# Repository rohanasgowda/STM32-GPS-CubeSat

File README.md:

# STM32-GPS-CubeSat

Custom STM32-based PCB design featuring GPS-related signal connections and peripheral connectivity, designed using KiCad. This repository contains the KiCad source files, generated manufacturing outputs, bill of materials, design reports, and board visualizations.

## Project overview

The design is centered on an STM32F407VGTx microcontroller. The schematic and board provide labeled connections for GPS- and radio-related signals, microSD, an OLED display, debugging, and power input. The repository documents the PCB design; it does not establish that the board has been assembled, programmed, or functionally tested.

## Project objectives

- Organize the KiCad schematic and PCB design for review and reuse.
- Provide the interfaces and connector signals represented in the schematic, including GPS-, radio-, storage-, display-, debug-, and power-related connections.
- Include the generated Gerber/drill outputs, BOM, design-check reports, and board views alongside the design sources.

These points describe the files in this repository and do not imply verified operation of attached modules or systems.

## Hardware specifications

- **Main component:** STM32F407VGTx, shown as U1 in the schematic and BOM; the BOM identifies an LQFP-100 footprint.
- **Other listed components:** passive capacitors and resistors, a push-button switch, and connectors for the interfaces named below.
- **Power:** the schematic/BOM identify an `EPS_POWER_INPUT` connector. No input-voltage range or power-performance specification is stated in the supplied files.

## PCB design overview

KiCad design sources are in `Hardware/Schematic/` and `Hardware/PCB/`. The supplied fabrication outputs include front- and back-copper, solder-mask, paste, silkscreen, and edge-cut Gerbers. PCB renderings and layer illustrations are provided below.

## Communication interfaces

The schematic labels include:

- **microSD (SPI-labeled signals):** `SD_MOSI`, `SD_MISO`, `SD_SCK`, and `SD_CS`; the BOM lists a `MICROSD_SPI` connector.
- **OLED (I²C-labeled signals):** `OLED_SDA` and `OLED_SCL`; the BOM lists an `OLED_I2C` connector.
- **GPS-related labels:** `GPS_TX`, `GPS_RX`, and `GPS_1PPS`.
- **Radio-related labels:** `RADIO_TX` and `RADIO_RX`.
- **Debug:** `SWDIO'` and `SWCLK` labels and a `SWD_DEBUG` connector are present.

These are labels/connectors in the design files; no protocol configuration, attached module, or functional test result is asserted here.

## PCB 3D visualizations

| Front | Back |
|---|---|
|  |  |

## PCB layout images

| Front layer | Back layer |
|---|---|
|  |  |

## Repository structure

```text
README.md
Hardware/
├── Schematic/       KiCad schematic
├── PCB/             KiCad board and project settings
│   └── Gerber/      Gerbers, drill files, and Gerber job file
├── BOM/             Bill of materials CSV
└── Design_Reports/  ERC and DRC reports
Images/              PCB renderings and layer views
```

## Manufacturing files

Generated manufacturing outputs are in `Hardware/PCB/Gerber/`: the `.gbr` layer files, `.drl` plated/non-plated drill files, and `.gbrjob` job file. Confirm these outputs against the intended manufacturer and the current design before ordering; their presence alone is not a fabrication-readiness claim.

## Design verification

The included ERC report records **0 errors and 0 warnings**. The included DRC report records **0 DRC violations**, but also reports **64 unconnected pads**. These reports are dated 2026-10-23 and are provided as captured; they do not establish that the design is fabrication-ready. Review the unconnected pads and rerun checks on the final design before fabrication.

## Excluded files

KiCad local settings, lock files, autosaves, backups, and temporary files are excluded from version control. The original workspace also contains unrelated documents; they are not part of this repository.

## License

The hardware design files in this repository are provided under the CERN Open Hardware Licence Version 2 - Permissive (CERN-OHL-P-2.0). See [LICENSE](LICENSE) for the full text.

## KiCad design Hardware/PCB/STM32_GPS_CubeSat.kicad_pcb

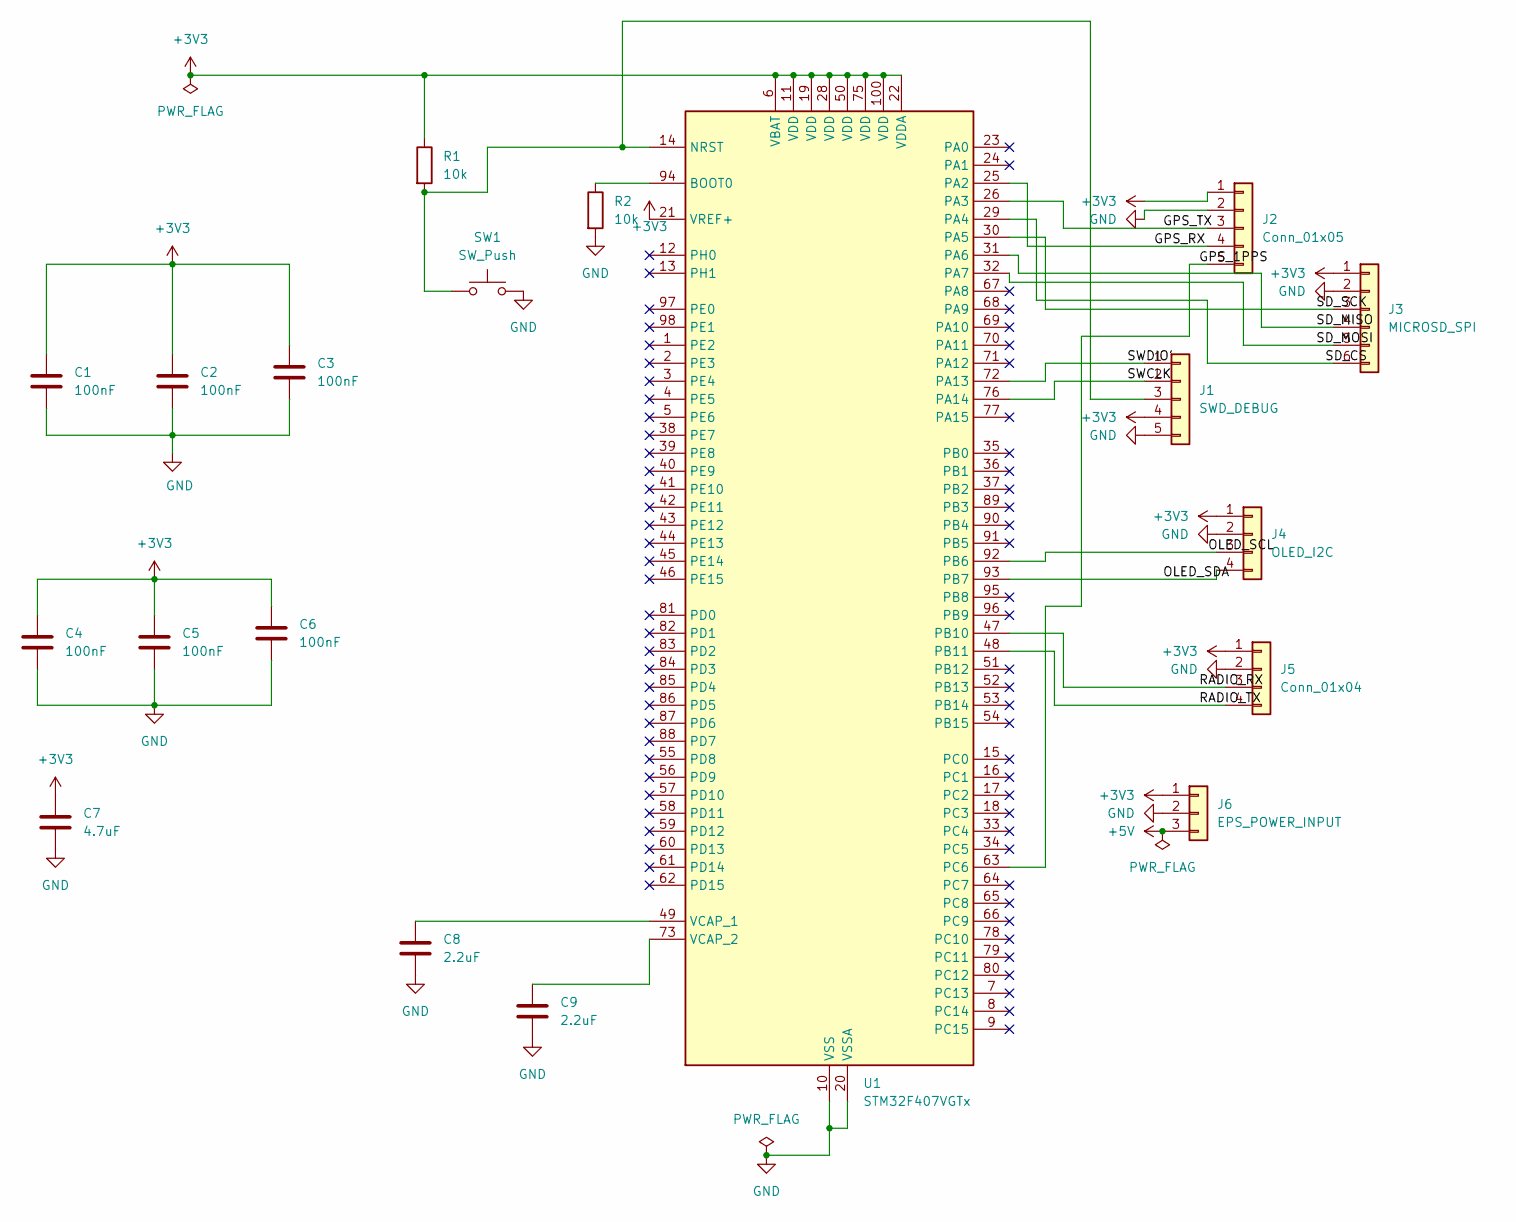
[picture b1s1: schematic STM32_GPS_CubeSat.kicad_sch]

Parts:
C1, C2, C3, C4, C5, C6: 100nF; C_0805_2012Metric
C7: 4.7uF; C_0805_2012Metric
C8, C9: 2.2uF; C_0805_2012Metric
J1: SWD_DEBUG; PinHeader_1x05_P2.54mm_Vertical
J2: Conn_01x05; PinHeader_1x05_P2.54mm_Vertical
J3: MICROSD_SPI; PinHeader_1x06_P2.54mm_Vertical
J4: OLED_I2C; PinHeader_1x04_P2.54mm_Vertical
J5: Conn_01x04; PinHeader_1x04_P2.54mm_Vertical
J6: EPS_POWER_INPUT; PinHeader_1x03_P2.54mm_Vertical
R1, R2: 10k; R_0805_2012Metric
SW1: SW_Push; SW_PUSH_6mm
U1: STM32F407VGTx; LQFP-100_14x14mm_P0.5mm

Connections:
+3V3: C1.1, C2.1, C3.1, C4.1, C5.1, C6.1, C7.1, J1.4, J2.1, J3.1, J4.1, J5.1, J6.1, R1.1, U1.6 (VBAT), U1.11 (VDD), U1.19 (VDD), U1.21 (VREF+), U1.22 (VDDA), U1.28 (VDD), U1.50 (VDD), U1.75 (VDD), U1.100 (VDD)
+5V: J6.3
/GPS_1PPS: J2.5, U1.63 (PC6)
/GPS_RX: J2.4, U1.25 (PA2)
/GPS_TX: J2.3, U1.26 (PA3)
/OLED_SCL: J4.3, U1.92 (PB6)
/OLED_SDA: J4.4, U1.93 (PB7)
/RADIO_RX: J5.3, U1.47 (PB10)
/RADIO_TX: J5.4, U1.48 (PB11)
/SD_CS: J3.6, U1.29 (PA4)
/SD_MISO: J3.4, U1.31 (PA6)
/SD_MOSI: J3.5, U1.32 (PA7)
/SD_SCK: J3.3, U1.30 (PA5)
/SWCLK: J1.2, U1.76 (PA14)
/SWDIO': J1.1, U1.72 (PA13)
GND: C1.2, C2.2, C3.2, C4.2, C5.2, C6.2, C7.2, C8.2, C9.2, J1.5, J2.2, J3.2, J4.2, J5.2, J6.2, R2.2, SW1.2, U1.10 (VSS), U1.20 (VSSA), U1.27 (VSS), U1.74 (VSS), U1.99 (VSS)
unnamed: J1.3, R1.2, SW1.1, U1.14 (NRST)
unnamed: R2.1, U1.94 (BOOT0)
unnamed: C8.1, U1.49 (VCAP_1)
unnamed: C9.1, U1.73 (VCAP_2)

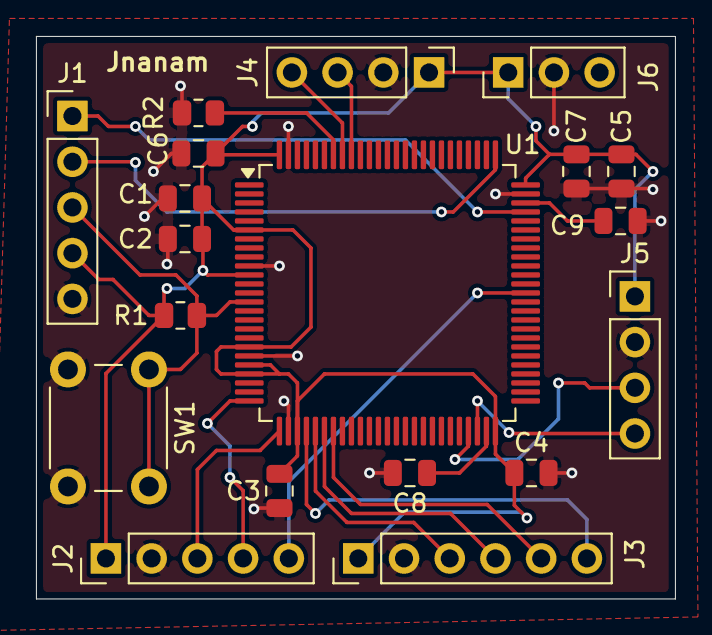
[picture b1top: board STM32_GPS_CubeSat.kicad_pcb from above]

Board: 2 copper layers, 35.5 x 31.2 mm, 19 parts (0 on the bottom side), 19 nets.

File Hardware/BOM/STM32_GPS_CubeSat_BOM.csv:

"Reference","Qty","Value","DNP","Exclude from BOM","Exclude from Board","Exclude from Simulation","Exclude from Position Files","Footprint","Datasheet"
"C1,C2,C3,C4,C5,C6","6","100nF","","","","","${EXCLUDE_FROM_POS_FILES}","Capacitor_SMD:C_0805_2012Metric",""
"C7","1","4.7uF","","","","","${EXCLUDE_FROM_POS_FILES}","Capacitor_SMD:C_0805_2012Metric",""
"C8,C9","2","2.2uF","","","","","${EXCLUDE_FROM_POS_FILES}","Capacitor_SMD:C_0805_2012Metric",""
"J1","1","SWD_DEBUG","","","","","${EXCLUDE_FROM_POS_FILES}","Connector_PinHeader_2.54mm:PinHeader_1x05_P2.54mm_Vertical",""
"J2","1","Conn_01x05","","","","","${EXCLUDE_FROM_POS_FILES}","Connector_PinHeader_2.54mm:PinHeader_1x05_P2.54mm_Vertical",""
"J3","1","MICROSD_SPI","","","","","${EXCLUDE_FROM_POS_FILES}","Connector_PinHeader_2.54mm:PinHeader_1x06_P2.54mm_Vertical",""
"J4","1","OLED_I2C","","","","","${EXCLUDE_FROM_POS_FILES}","Connector_PinHeader_2.54mm:PinHeader_1x04_P2.54mm_Vertical",""
"J5","1","Conn_01x04","","","","","${EXCLUDE_FROM_POS_FILES}","Connector_PinHeader_2.54mm:PinHeader_1x04_P2.54mm_Vertical",""
"J6","1","EPS_POWER_INPUT","","","","","${EXCLUDE_FROM_POS_FILES}","Connector_PinHeader_2.54mm:PinHeader_1x03_P2.54mm_Vertical",""
"R1,R2","2","10k","","","","","${EXCLUDE_FROM_POS_FILES}","Resistor_SMD:R_0805_2012Metric",""
"SW1","1","SW_Push","","","","","${EXCLUDE_FROM_POS_FILES}","Button_Switch_THT:SW_PUSH_6mm",""
"U1","1","STM32F407VGTx","","","","","${EXCLUDE_FROM_POS_FILES}","Package_QFP:LQFP-100_14x14mm_P0.5mm","https://www.st.com/resource/en/datasheet/stm32f407vg.pdf"
